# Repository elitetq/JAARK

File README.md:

# JAARK

A Bluetooth tank-style RC car with its own handheld controller, built on two STM32F446 Nucleo boards. JAARK carries a Colpitts oscillator metal detector, an ultrasonic range finder, headlights and a buzzer, and streams live telemetry back to an LCD on the controller.

Built by Team 28 for ENEL 300 at the University of Calgary (Winter 2026): Affaan Aamir, Jonart Bajraktari, Rohan Friesen, Karim Khodr and Abdul Qureshi. The name comes from our first initials.

## Contents

- [Who did what](#who-did-what)
- [System overview](#system-overview)
- [Hardware](#hardware)
- [Firmware](#firmware)
- [Pin map](#pin-map)
- [Repository layout](#repository-layout)
- [Building and flashing](#building-and-flashing)
- [Limitations and next steps](#limitations-and-next-steps)

## Who did what

| Area | Owner |
| --- | --- |
| All firmware on both boards: Bluetooth link, Fletcher-16 checksums, watchdog, driving, sensors, metal detection algorithm, LCD driver and UI | Jonart Bajraktari |
| Vehicle PCB (KiCad, this repo) | Jonart Bajraktari |
| Colpitts oscillator for the metal detector | Jonart Bajraktari |
| Controller PCB (Altium), chassis, drivetrain and enclosures | Teammates |

## System overview

The controller reads two joysticks and a headlight button, packs them into a 4 byte packet and sends it to the car over a pair of HC-05 modules. The car drives its tracks from that packet and replies with a 7 byte packet carrying the ultrasonic distance and the metal detector flag. Both directions are checked with a Fletcher-16 checksum and both boards run a watchdog on the link.

## Hardware

### Vehicle PCB

The vehicle board is a KiCad carrier for the Nucleo. It holds the battery protection, two DRV8231 H-bridge drivers for the 12 V track motors, the HC-05 module, test points and connectors for the metal detector, ultrasonic sensor and motors.

- **Battery protection:** a P-channel MOSFET blocks a reversed battery, a 15 V TVS diode clamps transients and a 10 µF capacitor provides bulk decoupling on the 12 V rail
- **Motor drivers:** two DRV8231 (4.5 V to 33 V, 3.7 A peak), one per track. A 0.2 Ω sense resistor on each caps the output at about 1.6 A, above the 1.2 A stall current of the Cytron SPG30E-270K motors
- **Trace widths:** 2 mm for the battery and motor current paths (IPC-2221), 0.75 mm for 5 V and 0.5 mm for 3.3 V
- **Thermal and noise:** pours on GND and +12 V, driver thermal pads tied to the ground plane, high-current parts on the perimeter and HC-05 routing kept away from the drivers

The 12 V 2800 mAh Li-ion pack is rated for 3 A continuous, which covers both motors at stall plus about 0.5 A of logic. Worst case runtime:

$$t = \frac{2800\ \text{mAh}}{2(1.2\ \text{A}) + 0.5\ \text{A}} \approx 58\ \text{min}$$

In practice the motors start to sag at around 20% charge, so a full run is closer to 45 minutes.

### Colpitts oscillator metal detector

The detector is a common-emitter Colpitts oscillator with a 22 mH search coil mounted under the chassis. The tank is the coil in parallel with two 1 nF capacitors in series:

$$f_0 = \frac{1}{2\pi\sqrt{L\,\frac{C_1 C_2}{C_1 + C_2}}} = \frac{1}{2\pi\sqrt{22\ \text{mH} \cdot 0.5\ \text{nF}}} \approx 48\ \text{kHz}$$

Metal near the coil changes its inductance and moves that frequency:

$$\frac{\Delta f}{f_0} \approx -\frac{1}{2}\,\frac{\Delta L}{L}$$

The faint sine output is AC coupled (5 nF) onto a 2.5 V bias, compared against 2.5 V by an LM339 and level shifted to a clean 3.3 V square wave by an NPN stage. The STM32 then times each rising edge with a 32-bit input capture timer, so the analog side never needs an amplitude detector or a long conditioning chain.

The circuit is the most sensitive part of the car. Supply noise, parasitics and nearby copper all pull the frequency, so it is kept away from the motors, battery and main PCB, and the coil is glued and taped down so vibration does not read as metal.

## Firmware

Everything is C on the STM32 HAL. Time-critical work (UART, sensor timing, watchdog) runs in hardware peripherals and interrupts, and the main loop handles decisions and outputs.

### Bluetooth link and checksums

- Two HC-05 modules in a master and slave pair over UART at 9600 baud
- Receive runs on DMA with IDLE line detection (`HAL_UARTEx_ReceiveToIdle_DMA`) and the half-transfer interrupt turned off, so one callback fires per frame
- Every packet ends in a Fletcher-16 checksum. A frame that fails is dropped and the receiver enters **hunt mode**: it shifts its buffer left by one byte and asks DMA for one more byte until the checksum lines up again

### Watchdog

A 16-bit timer (TIM3) runs on both boards and only a packet with a valid checksum resets it. If it overflows, the car sets all four motor PWM channels to zero, aborts and cleans up the UART, re-arms DMA and keeps pinging until a valid packet arrives. The controller shows a red watchdog screen with a reconnect animation over the same period. This was tested by cutting the link in several different ways and checking that the car always stopped and recovered.

### Driving

Each stick controls one track, like a real tank. The controller sends each stick as 4 bits, the car smooths the value with an exponential filter, applies a deadband around centre and maps the rest to 40% to 90% duty on one of the two DRV8231 inputs. PWM runs at 1 kHz from TIM8, TIM10 and TIM11.

### Ultrasonic distance

The car fires a 10 µs trigger pulse at the HC-SR04, then timestamps both edges of the echo on a 32-bit timer through an EXTI interrupt. Distance follows from the round trip time at 343 m/s:

$$d = \frac{v\,t}{2}$$

The reading is packed as a float into the 7 byte reply, and the controller smooths it before display.

### Metal detection algorithm

TIM5 captures each rising edge of the comparator output, and the gap between captures gives the frequency, $f = 84\ \text{MHz} / \Delta\text{ticks}$. At boot the firmware calibrates a baseline over 500 samples. After that it keeps two exponential moving averages of the frequency, a fast one ($\alpha = 0.2$) and a slow one ($\alpha = 0.085$). Slow drift moves both averages together, while metal moves the fast one first. When the fast average leads the slow one by more than 200 Hz, the car sounds the buzzer (2 kHz PWM on TIM12), sets the metal flag in its next packet and holds off for 0.8 s on TIM4.

### Controller display

The controller drives its SPI LCD with a custom ILI9341 driver that only redraws the regions that changed, which keeps CPU time free for the link. The screen shows headlight state, distance, both stick levels as bars, metal detection alerts and the watchdog screen. Font tables come from an open-source library, and `cnv_to_bit.py` converts PNG glyphs and images into raw bitmaps.

## Pin map

**Vehicle (STM32F446, `STM32/PCB_MOTOR_STM`)**

| Function | Pin | Peripheral |
| --- | --- | --- |
| HC-05 TX / RX | PA9 / PA10 | USART1 |
| Left track forward / reverse | PB8 / PB9 | TIM10 CH1 / TIM11 CH1 |
| Right track forward / reverse | PC8 / PC6 | TIM8 CH3 / TIM8 CH1 |
| Metal detector input | PA0 | TIM5 CH1 input capture |
| Buzzer | PB14 | TIM12 CH1 |
| HC-SR04 trigger / echo | PB4 / PB10 | GPIO / EXTI10 + TIM2 |
| Headlights | PB7 | GPIO |

**Controller (STM32F446, `STM32/STM32_CONTROLLER`)**

| Function | Pin | Peripheral |
| --- | --- | --- |
| HC-05 TX / RX | PA9 / PA10 | USART1 |
| Right stick / left stick | PA0 / PC4 | ADC1 IN0 / ADC2 IN14 |
| Joystick buttons (headlight toggle) | PC3, PB4 | GPIO |
| LCD SCK / MOSI | PB13 / PB15 | SPI2 |

## Repository layout

```
JAARK/
├── PCB/JAARK_PCB_MOTOR/      KiCad 9 vehicle board: schematic, layout, BOM, Gerbers in production/
├── STM32/PCB_MOTOR_STM/      vehicle firmware (CubeMX project with CMake presets)
├── STM32/STM32_CONTROLLER/   controller firmware (STM32CubeIDE project)
├── cnv_to_bit.py             PNG to raw bitmap converter for the LCD
└── docs/images/              figures used in this README
```

## Building and flashing

1. Open `STM32/PCB_MOTOR_STM` or `STM32/STM32_CONTROLLER` in STM32CubeIDE (File > Import > Existing Projects). The vehicle project also builds with CMake and the GNU Arm toolchain:
   ```bash
   cd STM32/PCB_MOTOR_STM
   cmake --preset Debug
   cmake --build --preset Debug
   ```
2. Flash each Nucleo over its onboard ST-LINK.
3. Pair the two HC-05 modules as master and slave at 9600 baud before the first run.
4. Power the car with the detector coil away from metal. It calibrates the detector for about 5 seconds, then waits for the first packet from the controller.

## Limitations and next steps

- The onboard 12 V to 5 V buck regulator was inconsistent, so the final build takes 5 V from the Nucleo regulator instead. A respin would fix the regulator layout.
- Most firmware lives in one main loop with flag polling. Splitting each subsystem into its own module, or moving to a state machine, would make it easier to extend.
- The link has no acknowledgements or sequence numbers. The checksum and watchdog catch bad or missing data, but they cannot tell a late packet from a fresh one.

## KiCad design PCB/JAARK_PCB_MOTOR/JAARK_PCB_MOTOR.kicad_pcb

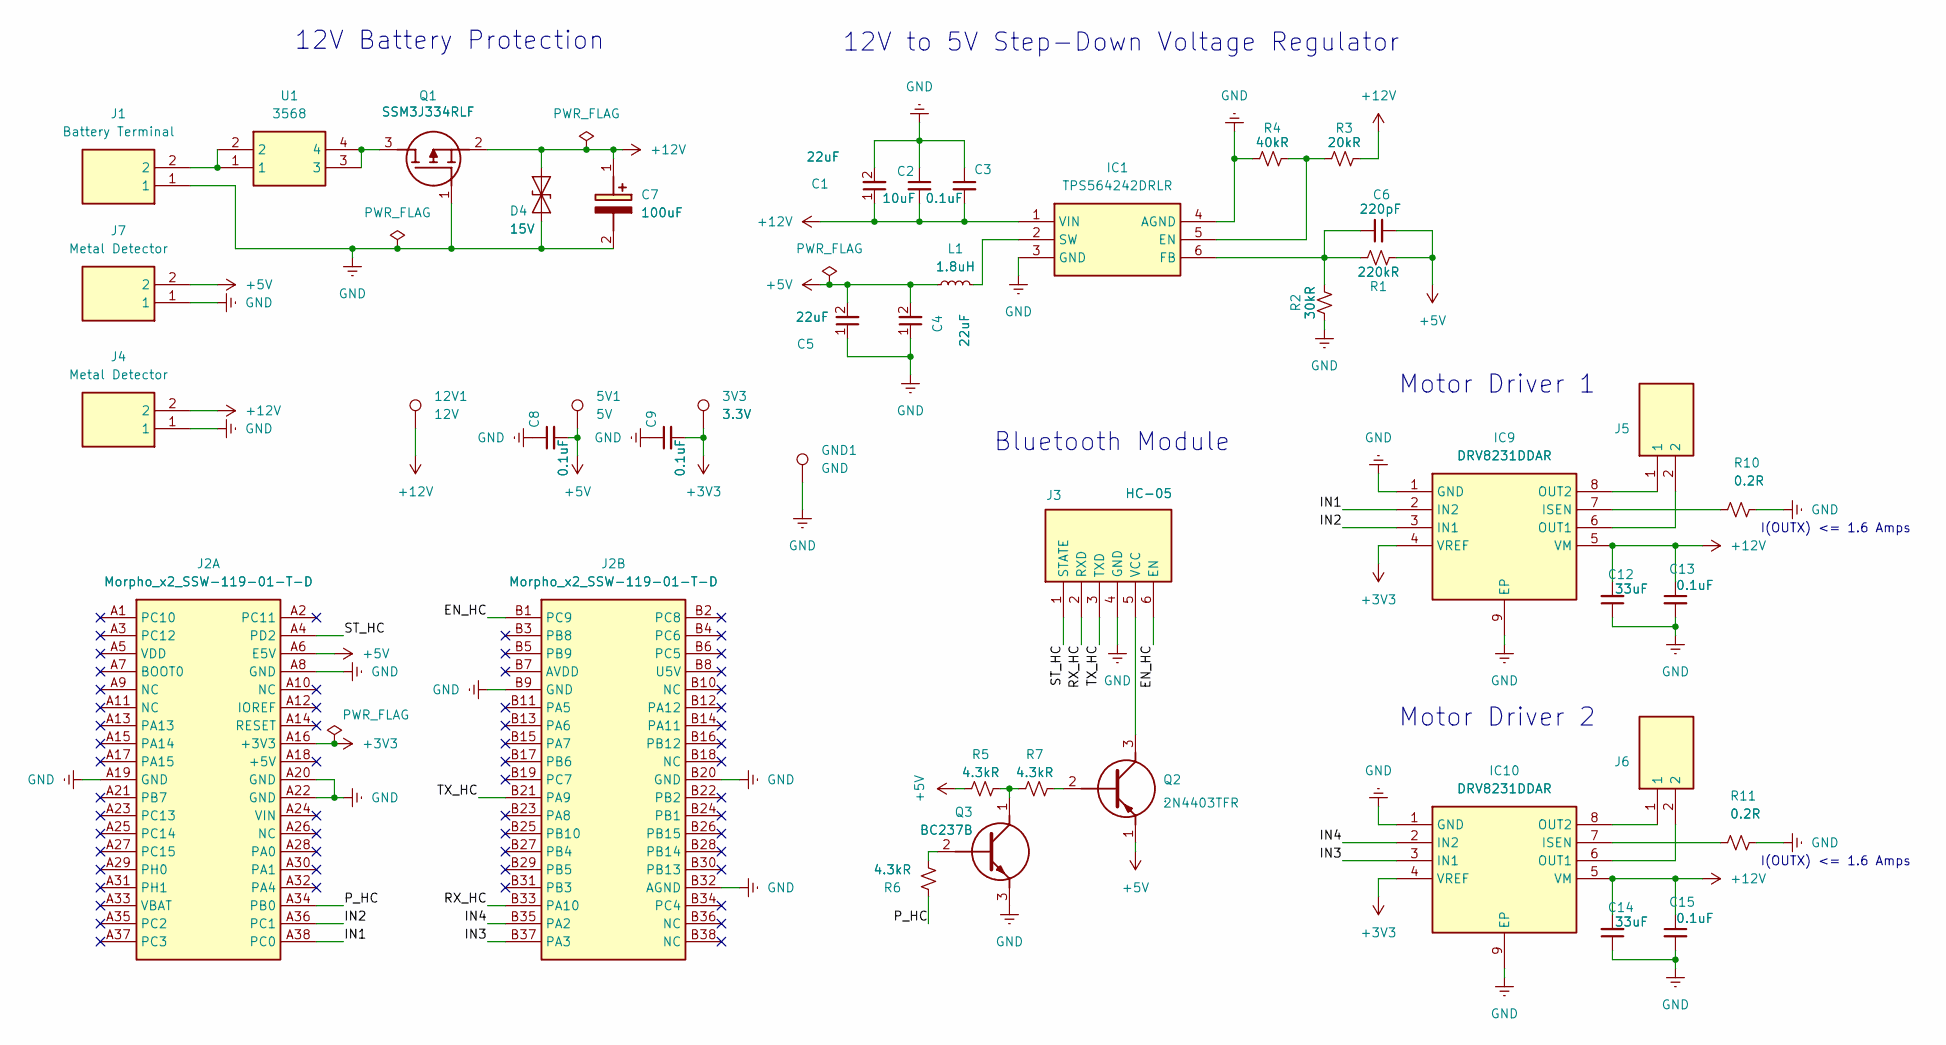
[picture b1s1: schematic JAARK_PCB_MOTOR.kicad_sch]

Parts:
3V3: 3.3V; TestPoint_Pad_1.5x1.5mm
5V1: 5V; TestPoint_Pad_1.5x1.5mm
12V1: 12V; TestPoint_Pad_1.5x1.5mm
C1: 22uF; CAPC2012X95N; MPN CL21A226MAYNNNE; Mouser Part Number 187-CL21B104KBCNNNC
C2: 10uF; CAPC2012X145N; Manufacturer_Part_Number CL21A106KAYNNNG; Mouser Part Number 187-CL21A106KAYNNNG
C3, C8, C9, C13, C15: 0.1uF; C0805; Manufacturer_Part_Number C0805C104K5RACTU; Mouser Part Number 80-C0805C104K5R
C4, C5: 22uF; CAPC2012X95N; Manufacturer_Part_Number CL21B104KBCNNNC; Mouser Part Number 187-CL21B104KBCNNNC
C6: 220pF; CAPC2012X75N; Manufacturer_Part_Number CL21C221JBANNNC; Mouser Part Number 187-CL21C221JBANNNC
C7: 100uF; CAPAE660X800N; Manufacturer_Part_Number UWT1V101MCL1GS; Mouser Part Number 647-UWT1V101MCL1S
C12, C14: 33uF; CAPC3216X180N; Manufacturer_Part_Number C3216X5R1E336M160AC; Mouser Part Number 810-C3216X5R1E336M
D4: 15V; SODFL3616X135N; Manufacturer_Part_Number SMF12CA
GND1: GND; TestPoint_Pad_1.5x1.5mm
IC1: TPS564242DRLR; SOTFL50P160X60-6N; Manufacturer_Part_Number TPS564242DRLR; Mouser Part Number 595-TPS564242DRLR
IC9, IC10: DRV8231DDAR; SOIC127P600X170-9N; Manufacturer_Part_Number DRV8231DDAR; Mouser Part Number 595-DRV8231DDAR
J1: Battery Terminal; 1984617; Manufacturer_Part_Number 1984617; Mouser Part Number 651-1984617
J2: Morpho_x2_SSW-119-01-T-D; STM_Nucleo_Morpho_x2_Footprint; Manufacturer_Part_Number SSW-119-01-T-D; Mouser Part Number 200-SSW11901TD
J3: HC-05; PPPC061LGBNRC; Manufacturer_Part_Number PPPC061LGBN-RC
J4, J7: Metal Detector; 1984617; Manufacturer_Part_Number 1984617; Mouser Part Number 651-1984617
J5, J6: 1984617; Manufacturer_Part_Number 1984617; Mouser Part Number 651-1984617
L1: 1.8uH; INDPM4141X200N; Manufacturer_Part_Number 74438356018; Mouser Part Number 710-74438356018
Q1: SSM3J334RLF; 2SC2712GRLF; Manufacturer_Part_Number SSM3J334R,LF
Q2: 2N4403TFR; BC33740TA; Manufacturer_Part_Number 2N4403TFR; Mouser Part Number 512-2N4403TFR
Q3: BC237B; TO-92__TO-226_; Manufacturer_Part_Number BC237B; Mouser Part Number 512-BC237B
R1: 220kR; RESC2012X65N; Manufacturer_Part_Number CRG0805F220K; Mouser Part Number 279-CRG0805F220K
R2: 30kR; RESC2012X65N; Manufacturer_Part_Number CRG0805F30K; Mouser Part Number 279-CRG0805F30K
R3: 20kR; RESC2012X50N; Manufacturer_Part_Number RG2012P-203-B-T5; Mouser Part Number 754-RG2012P-203-B-T5
R4: 40kR; RESC2012X60N; Manufacturer_Part_Number RC0805FR-0740K2L; Mouser Part Number 603-RC0805FR-0740K2L
R5, R6, R7: 4.3kR; R_Axial_DIN0207_L6.3mm_D2.5mm_P10.16mm_Horizontal
R10, R11: 0.2R; RESC2013X65N; Manufacturer_Part_Number RL1220S-R20-F; Mouser Part Number 754-RL1220S-R20-F
U1: 3568; Manufacturer_Part_Number 3568; Mouser Part Number 534-3568

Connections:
+3V3: 3V3.1, C9.2, IC9.4 (VREF), IC10.4 (VREF), J2.A16 (+3V3)
+5V: 5V1.1, C4.2, C5.2, C6.2, C8.2, J2.A6 (E5V), J7.2, L1.1, Q2.1 (E), R1.1, R5.1
+12V: 12V1.1, C1.1, C2.2, C3.2, C7.1 (+), C12.2, C13.1, C14.2, C15.1, D4.2 (A2), IC1.1 (VIN), IC9.5 (VM), IC10.5 (VM), J4.2, Q1.2 (S), R3.1
/EN_HC: J2.B1 (PC9), J3.6 (EN)
/IN1: IC9.2 (IN2), J2.A38 (PC0)
/IN2: IC9.3 (IN1), J2.A36 (PC1)
/IN3: IC10.3 (IN1), J2.B37 (PA3)
/IN4: IC10.2 (IN2), J2.B35 (PA2)
/P_HC: J2.A34 (PB0), R6.1
/RX_HC: J2.B33 (PA10), J3.2 (RXD)
/ST_HC: J2.A4 (PD2), J3.1 (STATE)
/TX_HC: J2.B21 (PA9), J3.3 (TXD)
GND: C1.2, C2.1, C3.1, C4.1, C5.1, C7.2 (-), C8.1, C9.1, C12.1, C13.2, C14.1, C15.2, D4.1 (A1), GND1.1, IC1.3 (GND), IC1.4 (AGND), IC9.1 (GND), IC9.9 (EP), IC10.1 (GND), IC10.9 (EP), J1.1, J2.A8 (GND), J2.A19 (GND), J2.A20 (GND), J2.A22 (GND), J2.B9 (GND), J2.B20 (GND), J2.B32 (AGND), J3.4 (GND), J4.1, J7.1, Q1.1 (G), Q3.3 (E), R2.1, R4.2, R10.2, R11.2
unnamed: IC1.5 (EN), R3.2, R4.1
unnamed: C6.1, IC1.6 (FB), R1.2, R2.2
unnamed: IC1.2 (SW), L1.2
unnamed: IC9.7 (ISEN), R10.1
unnamed: IC9.6 (OUT1), J5.2
unnamed: IC9.8 (OUT2), J5.1
unnamed: IC10.7 (ISEN), R11.1
unnamed: IC10.6 (OUT1), J6.2
unnamed: IC10.8 (OUT2), J6.1
unnamed: J1.2, U1.1, U1.2
unnamed: J3.5 (VCC), Q2.3 (C)
unnamed: Q1.3 (D), U1.3, U1.4
unnamed: Q2.2 (B), R7.2
unnamed: Q3.2 (B), R6.2
unnamed: Q3.1 (C), R5.2, R7.1

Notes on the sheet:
I(OUTX) <= 1.6 Amps
Bluetooth Module
Motor Driver 2
12V to 5V Step-Down Voltage Regulator
Motor Driver 1
12V Battery Protection

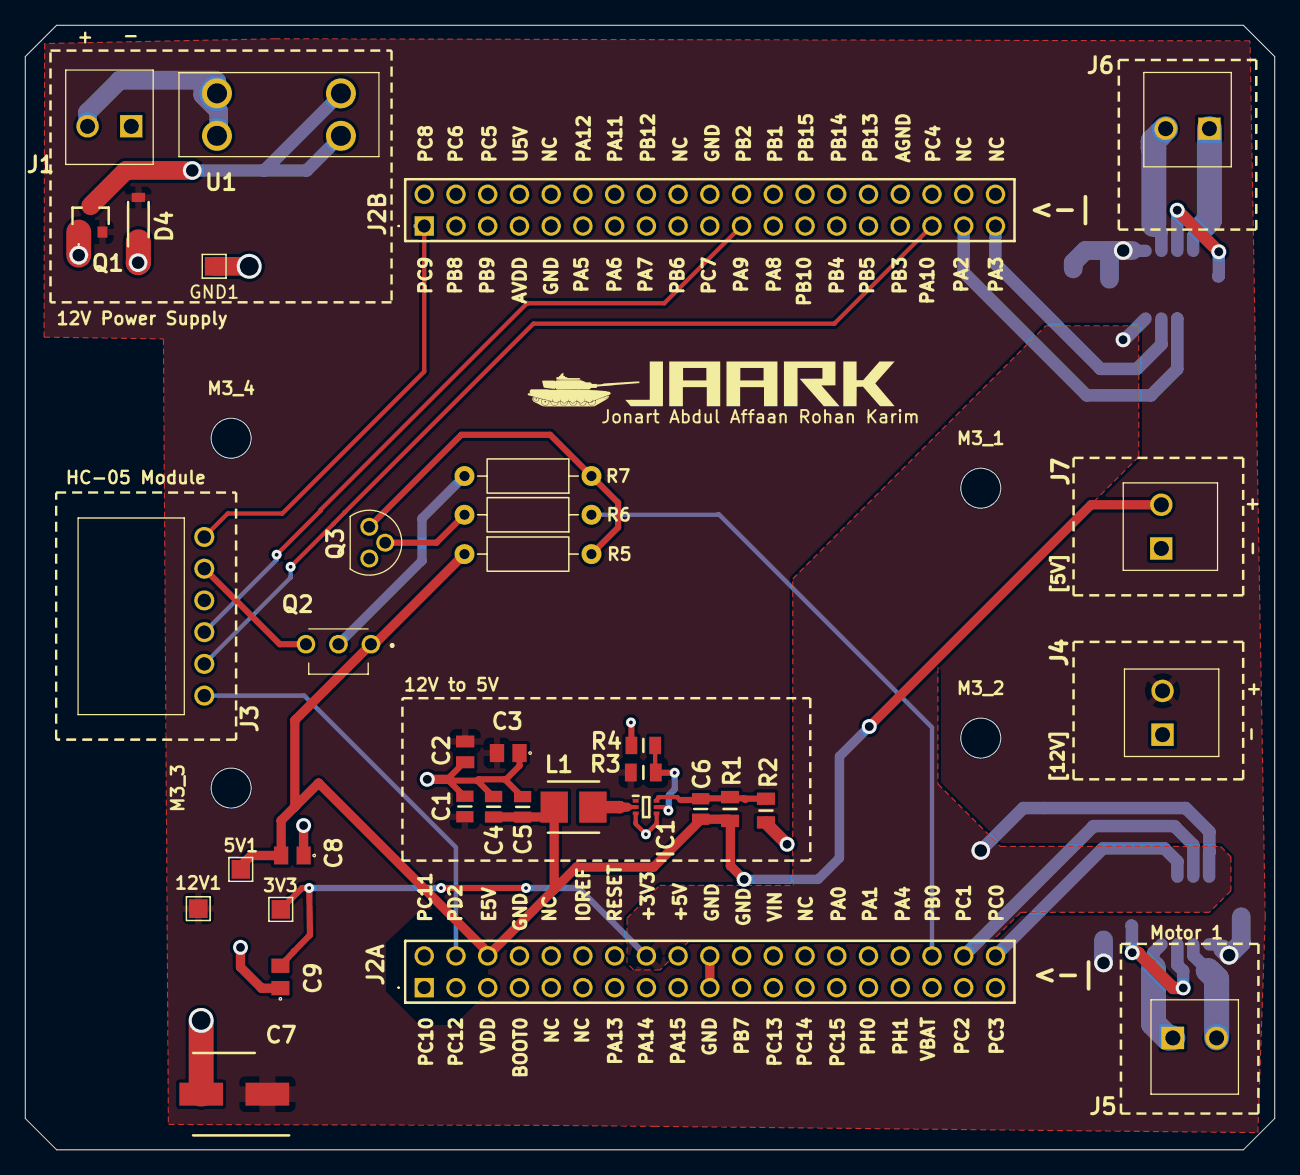
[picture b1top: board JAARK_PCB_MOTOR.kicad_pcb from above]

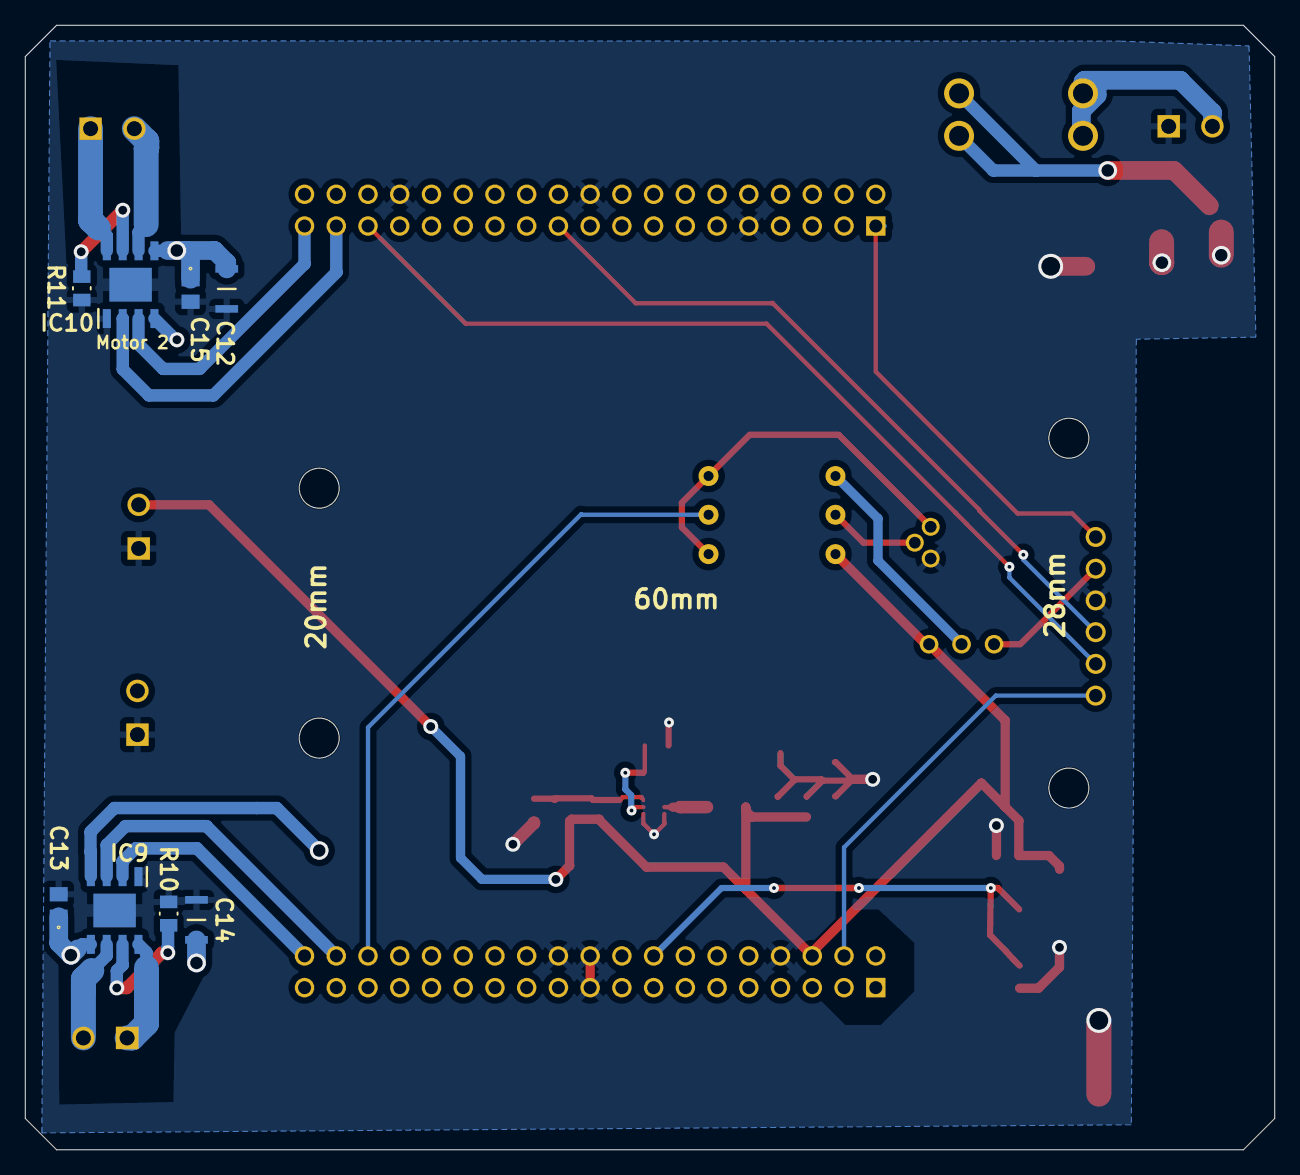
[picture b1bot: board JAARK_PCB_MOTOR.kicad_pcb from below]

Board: 2 copper layers, 100.0 x 90.0 mm, 46 parts (8 on the bottom side), 28 nets.

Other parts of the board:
M3_1: M3_1; MountingHole_3.2mm_M3
M3_2: M3_2; MountingHole_3.2mm_M3
M3_3: M3_3; MountingHole_3.2mm_M3
M3_4: M3_4; MountingHole_3.2mm_M3

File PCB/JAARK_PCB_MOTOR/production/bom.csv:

Designator,Footprint,Quantity,Value,LCSC Part #
C1,CAPC2012X95N,1,22uF,CL21A226MAYNNNE
"C12, C14",CAPC3216X180N,2,33uF,
"C13, C15, C3, C8, C9",C0805,5,0.1uF,
C2,CAPC2012X145N,1,10uF,
"C4, C5",CAPC2012X95N,2,22uF,
C6,CAPC2012X75N,1,220pF,
C7,CAPAE660X800N,1,100uF,
D4,SODFL3616X135N,1,15V,
IC1,SOTFL50P160X60-6N,1,TPS564242DRLR,
"IC10, IC9",SOIC127P600X170-9N,2,DRV8231DDAR,
J1,1984617,1,Battery Terminal,
J2,STM_Nucleo_Morpho_x2_Footprint,1,Morpho_x2_SSW-119-01-T-D,
J3,PPPC061LGBNRC,1,HC-05,
"J4, J7",1984617,2,Metal Detector,
"J5, J6",1984617,2,~,
L1,INDPM4141X200N,1,1.8uH,
Q1,2SC2712GRLF,1,SSM3J334RLF,
Q2,BC33740TA,1,2N4403TFR,
Q3,TO-92__TO-226_,1,BC237B,
R1,RESC2012X65N,1,220kR,
"R10, R11",RESC2013X65N,2,0.2R,
R2,RESC2012X65N,1,30kR,
R3,RESC2012X50N,1,20kR,
R4,RESC2012X60N,1,40kR,
U1,3568,1,3568,

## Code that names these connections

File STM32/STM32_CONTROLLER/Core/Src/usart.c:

/* USER CODE BEGIN Header */
/**
  ******************************************************************************
  * @file    usart.c
  * @brief   This file provides code for the configuration
  *          of the USART instances.
  ******************************************************************************
  * @attention
  *
  * Copyright (c) 2026 STMicroelectronics.
  * All rights reserved.
  *
  * This software is licensed under terms that can be found in the LICENSE file
  * in the root directory of this software component.
  * If no LICENSE file comes with this software, it is provided AS-IS.
  *
  ******************************************************************************
  */
/* USER CODE END Header */
/* Includes ------------------------------------------------------------------*/
#include "usart.h"

/* USER CODE BEGIN 0 */

/* USER CODE END 0 */

UART_HandleTypeDef huart1;
UART_HandleTypeDef huart2;
DMA_HandleTypeDef hdma_usart1_rx;

/* USART1 init function */

void MX_USART1_UART_Init(void)
{

  /* USER CODE BEGIN USART1_Init 0 */

  /* USER CODE END USART1_Init 0 */

  /* USER CODE BEGIN USART1_Init 1 */

  /* USER CODE END USART1_Init 1 */
  huart1.Instance = USART1;
  huart1.Init.BaudRate = 9600;
  huart1.Init.WordLength = UART_WORDLENGTH_8B;
  huart1.Init.StopBits = UART_STOPBITS_1;
  huart1.Init.Parity = UART_PARITY_NONE;
  huart1.Init.Mode = UART_MODE_TX_RX;
  huart1.Init.HwFlowCtl = UART_HWCONTROL_NONE;
  huart1.Init.OverSampling = UART_OVERSAMPLING_16;
  if (HAL_UART_Init(&huart1) != HAL_OK)
  {
    Error_Handler();
  }
  /* USER CODE BEGIN USART1_Init 2 */

  /* USER CODE END USART1_Init 2 */

}
/* USART2 init function */

void MX_USART2_UART_Init(void)
{

  /* USER CODE BEGIN USART2_Init 0 */

  /* USER CODE END USART2_Init 0 */

  /* USER CODE BEGIN USART2_Init 1 */

  /* USER CODE END USART2_Init 1 */
  huart2.Instance = USART2;
  huart2.Init.BaudRate = 38400;
  huart2.Init.WordLength = UART_WORDLENGTH_8B;
  huart2.Init.StopBits = UART_STOPBITS_1;
  huart2.Init.Parity = UART_PARITY_NONE;
  huart2.Init.Mode = UART_MODE_TX_RX;
  huart2.Init.HwFlowCtl = UART_HWCONTROL_NONE;
  huart2.Init.OverSampling = UART_OVERSAMPLING_16;
  if (HAL_UART_Init(&huart2) != HAL_OK)
  {
    Error_Handler();
  }
  /* USER CODE BEGIN USART2_Init 2 */

  /* USER CODE END USART2_Init 2 */

}

void HAL_UART_MspInit(UART_HandleTypeDef* uartHandle)
{

  GPIO_InitTypeDef GPIO_InitStruct = {0};
  if(uartHandle->Instance==USART1)
  {
  /* USER CODE BEGIN USART1_MspInit 0 */

  /* USER CODE END USART1_MspInit 0 */
    /* USART1 clock enable */
    __HAL_RCC_USART1_CLK_ENABLE();

    __HAL_RCC_GPIOA_CLK_ENABLE();
    /**USART1 GPIO Configuration
    PA9     ------> USART1_TX
    PA10     ------> USART1_RX
    */
    GPIO_InitStruct.Pin = GPIO_PIN_9|GPIO_PIN_10;
    GPIO_InitStruct.Mode = GPIO_MODE_AF_PP;
    GPIO_InitStruct.Pull = GPIO_NOPULL;
    GPIO_InitStruct.Speed = GPIO_SPEED_FREQ_VERY_HIGH;
    GPIO_InitStruct.Alternate = GPIO_AF7_USART1;
    HAL_GPIO_Init(GPIOA, &GPIO_InitStruct);

    /* USART1 DMA Init */
    /* USART1_RX Init */
    hdma_usart1_rx.Instance = DMA2_Stream2;
    hdma_usart1_rx.Init.Channel = DMA_CHANNEL_4;
    hdma_usart1_rx.Init.Direction = DMA_PERIPH_TO_MEMORY;
    hdma_usart1_rx.Init.PeriphInc = DMA_PINC_DISABLE;
    hdma_usart1_rx.Init.MemInc = DMA_MINC_ENABLE;
    hdma_usart1_rx.Init.PeriphDataAlignment = DMA_PDATAALIGN_BYTE;
    hdma_usart1_rx.Init.MemDataAlignment = DMA_MDATAALIGN_BYTE;
    hdma_usart1_rx.Init.Mode = DMA_NORMAL;
    hdma_usart1_rx.Init.Priority = DMA_PRIORITY_LOW;
    hdma_usart1_rx.Init.FIFOMode = DMA_FIFOMODE_DISABLE;
    if (HAL_DMA_Init(&hdma_usart1_rx) != HAL_OK)
    {
      Error_Handler();
    }

    __HAL_LINKDMA(uartHandle,hdmarx,hdma_usart1_rx);

  /* USER CODE BEGIN USART1_MspInit 1 */

  /* USER CODE END USART1_MspInit 1 */
  }
  else if(uartHandle->Instance==USART2)
  {
  /* USER CODE BEGIN USART2_MspInit 0 */

  /* USER CODE END USART2_MspInit 0 */
    /* USART2 clock enable */
    __HAL_RCC_USART2_CLK_ENABLE();

    __HAL_RCC_GPIOA_CLK_ENABLE();
    /**USART2 GPIO Configuration
    PA2     ------> USART2_TX
    PA3     ------> USART2_RX
    */
    GPIO_InitStruct.Pin = GPIO_PIN_2|GPIO_PIN_3;
    GPIO_InitStruct.Mode = GPIO_MODE_AF_PP;
    GPIO_InitStruct.Pull = GPIO_NOPULL;
    GPIO_InitStruct.Speed = GPIO_SPEED_FREQ_VERY_HIGH;
    GPIO_InitStruct.Alternate = GPIO_AF7_USART2;
    HAL_GPIO_Init(GPIOA, &GPIO_InitStruct);

    /* USART2 interrupt Init */
    HAL_NVIC_SetPriority(USART2_IRQn, 0, 0);
    HAL_NVIC_EnableIRQ(USART2_IRQn);
  /* USER CODE BEGIN USART2_MspInit 1 */

  /* USER CODE END USART2_MspInit 1 */
  }
}

void HAL_UART_MspDeInit(UART_HandleTypeDef* uartHandle)
{

  if(uartHandle->Instance==USART1)
  {
  /* USER CODE BEGIN USART1_MspDeInit 0 */

  /* USER CODE END USART1_MspDeInit 0 */
    /* Peripheral clock disable */
    __HAL_RCC_USART1_CLK_DISABLE();

    /**USART1 GPIO Configuration
    PA9     ------> USART1_TX
    PA10     ------> USART1_RX
    */
    HAL_GPIO_DeInit(GPIOA, GPIO_PIN_9|GPIO_PIN_10);

    /* USART1 DMA DeInit */
    HAL_DMA_DeInit(uartHandle->hdmarx);
  /* USER CODE BEGIN USART1_MspDeInit 1 */

  /* USER CODE END USART1_MspDeInit 1 */
  }
  else if(uartHandle->Instance==USART2)
  {
  /* USER CODE BEGIN USART2_MspDeInit 0 */

  /* USER CODE END USART2_MspDeInit 0 */
    /* Peripheral clock disable */
    __HAL_RCC_USART2_CLK_DISABLE();

    /**USART2 GPIO Configuration
    PA2     ------> USART2_TX
    PA3     ------> USART2_RX
    */
    HAL_GPIO_DeInit(GPIOA, GPIO_PIN_2|GPIO_PIN_3);

    /* USART2 interrupt Deinit */
    HAL_NVIC_DisableIRQ(USART2_IRQn);
  /* USER CODE BEGIN USART2_MspDeInit 1 */

  /* USER CODE END USART2_MspDeInit 1 */
  }
}

/* USER CODE BEGIN 1 */

/* USER CODE END 1 */

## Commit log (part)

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2026-01-28 Started initial progress on 5V step down circuit.
2026-02-01 Work on Motor Driver H-Bridge. May need to consider switching to MOSFET, as BJT's are not suitable for high amp loads. Could fry board or resistors with the current H-Bridge setup.
2026-02-02 Finished H-Bridge
2026-02-02 Organizing libraries in the local folder.
2026-02-03 Starting zephyr testing
2026-02-04 Motor driver recreation, appended footprints to lots of R,L,C elements
2026-02-04 Added random file
2026-02-04 Fixed footprints for sharing
2026-02-05 holy shit its working
2026-02-05 Struct creation for LCD display
2026-02-06 font creation almost there
2026-02-06 LCD screen is working!
2026-02-06 Better motor drivers, fixed capacitor in voltage regulation.
2026-02-07 PCB Motor V1 finished.
2026-02-07 Added mounting holes to Motor PCB, fixed up trace errors
2026-02-07 forgot one thing
2026-02-08 "Added heat sink"
2026-02-08 Added heat sink to PCB file and adjusted footprint
2026-02-08 More work on PCB, removed heatsink and then added mounting holes again
2026-02-09 Fixed motor positioning.
2026-02-09 Bluetooth module
2026-02-10 Motor PCB finished?
2026-02-10 added test points
2026-02-10 JLCPCB compatibility
2026-02-12 Final prototype of PCB
2026-03-01 Ultrasonic sensor code working on the STM32 with custom LCD driver
2026-03-04 Working code for ultrasonic
2026-03-14 Starting on CONTROLLER STM code
2026-03-16 Bluetooth connectivity and DMA added, as well as controller stm folder
2026-03-16 Bluetooth working
2026-03-16 Bluetooth working with joystick, DMA implementation
2026-03-23 Motor-side BT watchdog and distance sensor sending implemented, not tested
2026-03-23 Finished implementation of watchdog, code untested on the actual stms.
2026-03-23 Added screen rotation
2026-03-25 Working 2 way bt. working on display module
2026-03-25 Changing USART settings lemme commit before i implode all the code
2026-03-28 Made 2way work with bluetooth, also metal detector algorithm works with the sensor code and watchdog.
2026-03-30 Fletcher16 checksum working
2026-04-01 Working for sprint
2026-04-10 Working final product, going to try and change buzzer pin
2026-05-08 Final Software push
